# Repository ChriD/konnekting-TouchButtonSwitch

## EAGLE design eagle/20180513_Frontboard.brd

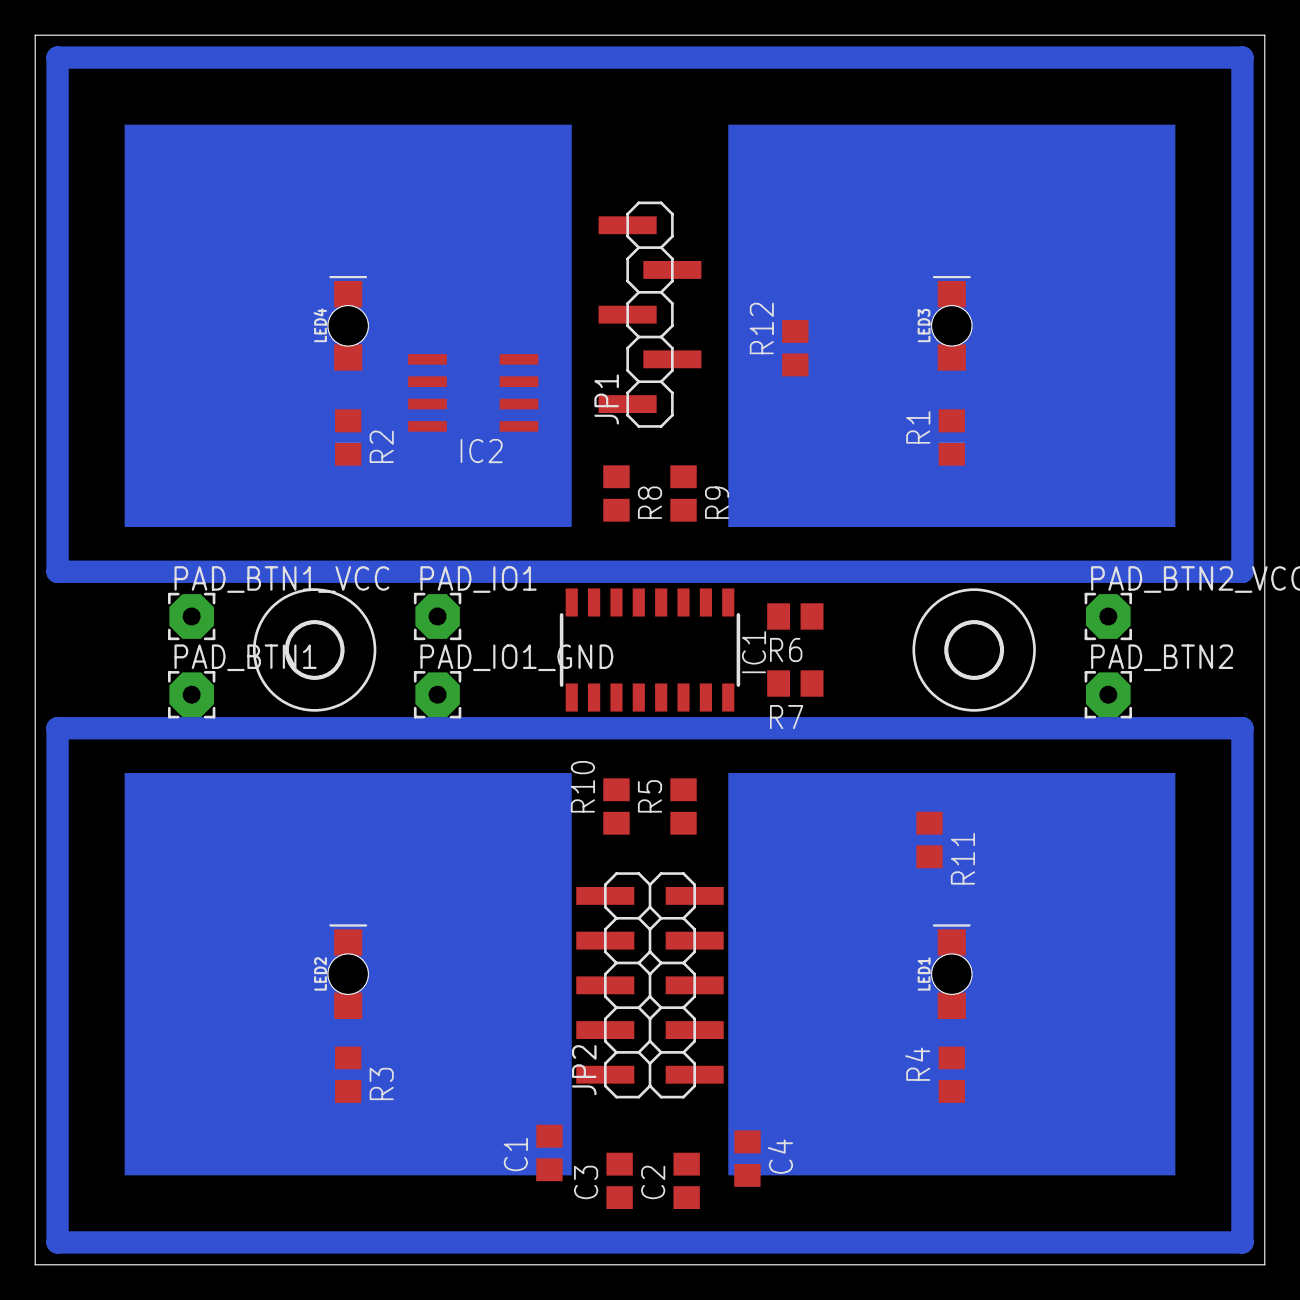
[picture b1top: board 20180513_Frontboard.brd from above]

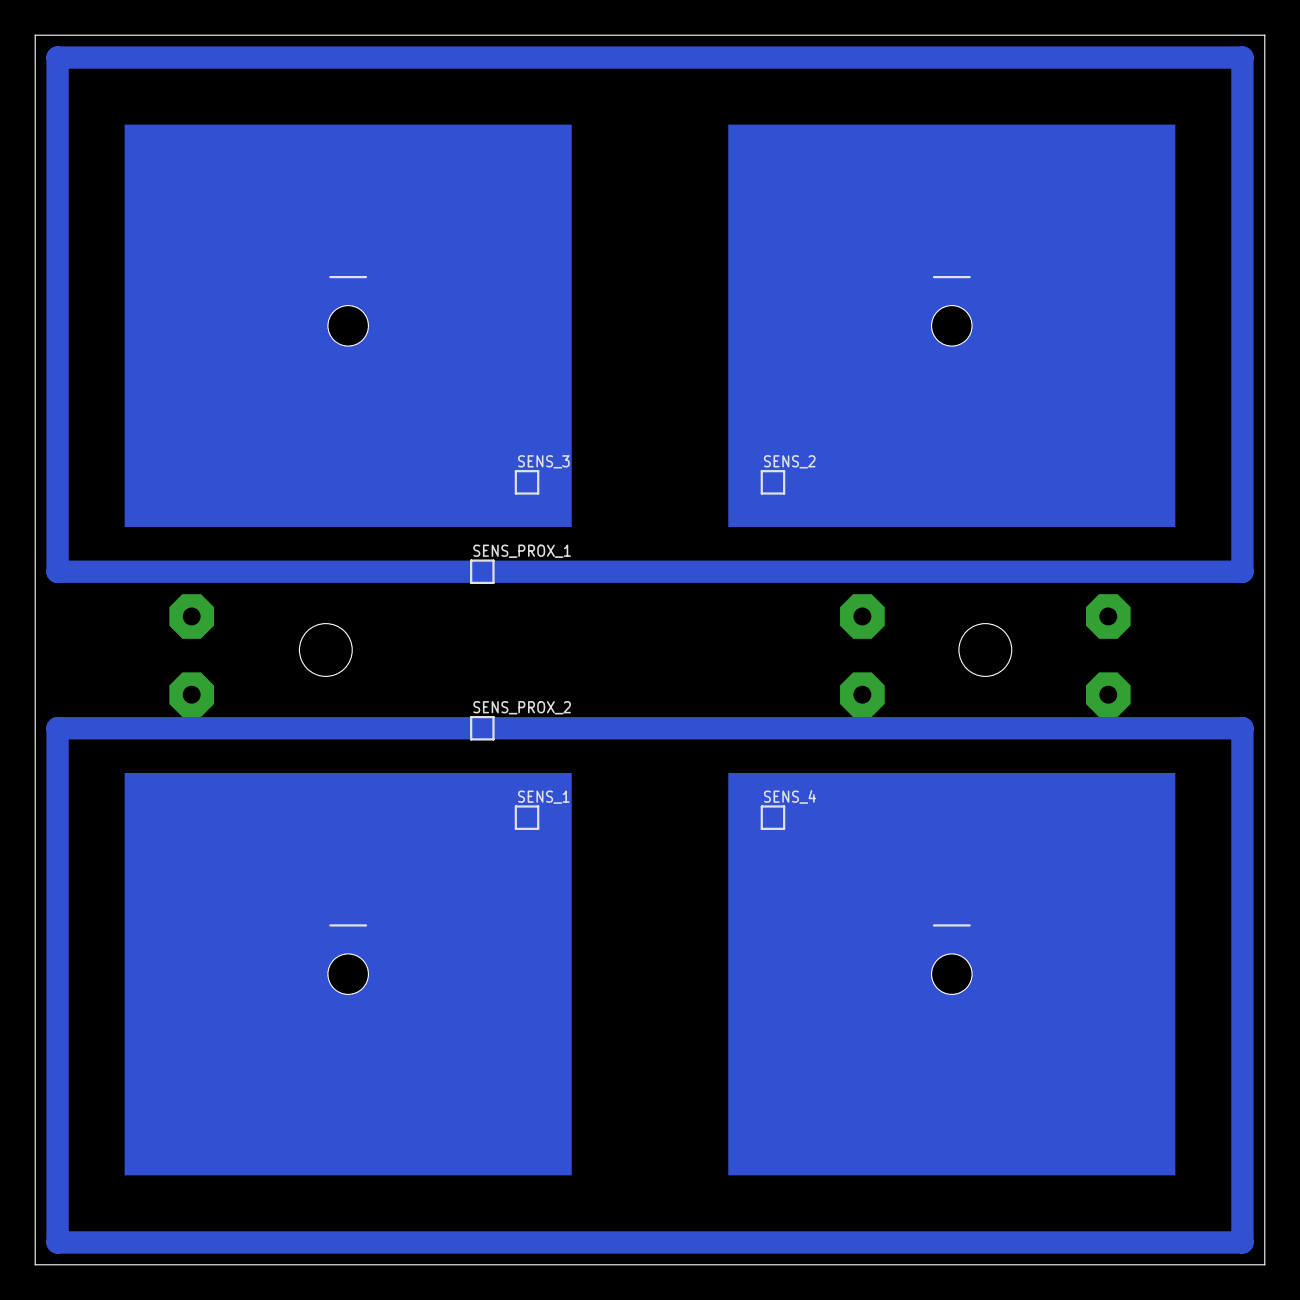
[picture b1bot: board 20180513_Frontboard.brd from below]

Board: 2 copper layers, 69.8 x 69.8 mm, 38 parts (6 on the bottom side), 33 nets.

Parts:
C1, C3: 0.1uf; C0805
C2: 1uf; C0805
C4: 2.2nf; C0805
IC1: CY8CMBR3110-SX2I; SOIC127P600X173-16N
IC2: LM35DM; SO08
JP1: I2C; 1X05SMD
JP2: IOS; 2X05SMD
LED1, LED2, LED3, LED4: WHITE; LED-1206-BOTTOM
PAD_BTN1, PAD_BTN1_VCC: BTN1; 2,54/1,0
PAD_BTN2, PAD_BTN2_VCC: BTN2; 2,54/1,0
PAD_IO1, PAD_IO1_GND: IO1; 2,54/1,0
R1, R2, R3, R4, R11, R12: 330E; R0805
R5, R6, R7, R8, R9, R10: 560E; R0805
SENS_1: SENS_1; WPAD-1-0603
SENS_2: SENS_2; WPAD-1-0603
SENS_3: SENS_3; WPAD-1-0603
SENS_4: SENS_4; WPAD-1-0603
SENS_PROX_1, SENS_PROX_2: SENS_PROX; WPAD-1-0603
U$1, U$2: 3,0

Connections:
BTN1: JP2.9, PAD_BTN1.1
BTN2: JP2.10, PAD_BTN2.1
GND: C1.2, C2.2, C3.2, C4.2, IC1.8, IC1.13, IC1.15, IC2.4, JP1.2, LED1.C, LED2.C, LED3.C, LED4.C, PAD_IO1_GND.1
HOST_INT: IC1.14, JP1.3
I2C_SCL: JP1.4, R11.2
I2C_SDA: JP1.5, R12.2
IO1: JP2.7, PAD_IO1.1
LED1: JP2.1, R4.1
LED2: JP2.2, R3.1
LED3: JP2.3, R1.1
LED4: JP2.4, R2.1
unnamed: IC1.9, R8.2
unnamed: IC1.10, R9.2
unnamed: IC1.11, R10.2
unnamed: IC1.1, R12.1
unnamed: IC1.2, R11.1
unnamed: IC1.3, R6.2
unnamed: IC1.12, R5.2
unnamed: C3.1, IC1.6
unnamed: C4.1, IC1.5
unnamed: IC1.4, R7.2
unnamed: LED4.A, R2.2
unnamed: LED1.A, R4.2
unnamed: LED2.A, R3.2
unnamed: LED3.A, R1.2
SENS_1: R5.1, SENS_1.1
SENS_2: R8.1, SENS_2.1
SENS_3: R9.1, SENS_3.1
SENS_4: R10.1, SENS_4.1
SENS_PROX_1: R6.1, SENS_PROX_1.1
SENS_PROX_2: R7.1, SENS_PROX_2.1
TMP: IC2.1, JP2.8
VCC: C1.1, C2.1, IC1.7, IC2.8, JP1.1, PAD_BTN1_VCC.1, PAD_BTN2_VCC.1

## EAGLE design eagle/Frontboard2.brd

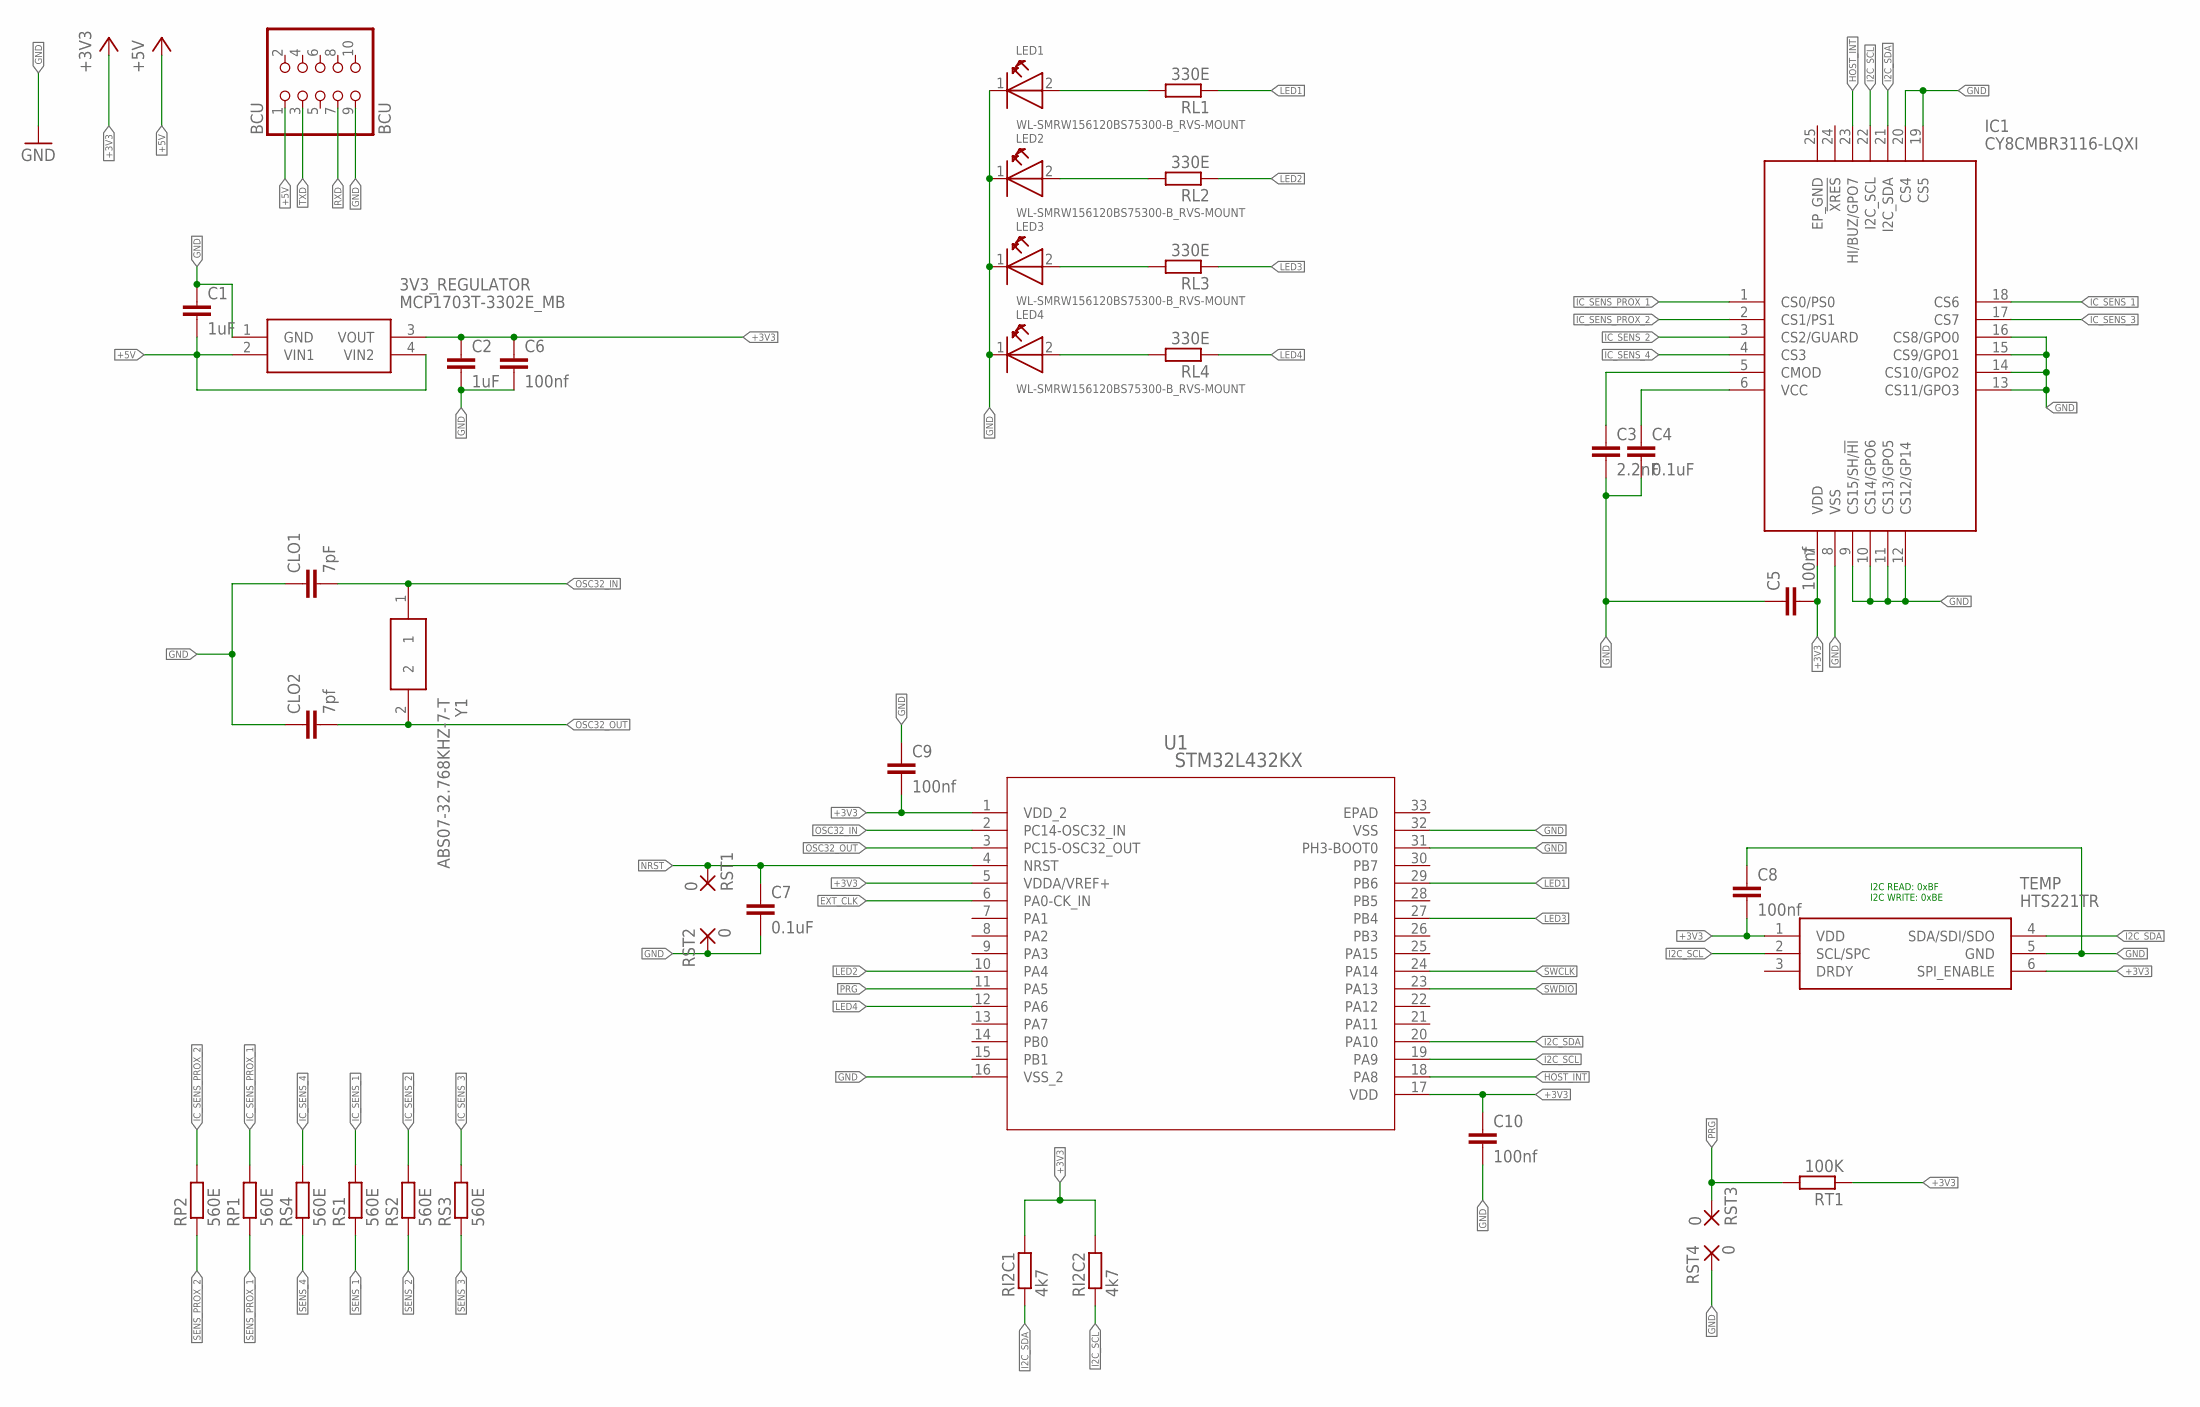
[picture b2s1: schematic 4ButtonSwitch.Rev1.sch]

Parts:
3V3_REGULATOR: MCP1703T-3302E_MB; SOT-89(MB)
BCU: BCU; 2X05SMD
C1, C2: 1uF; C0402
C3: 2.2nF; C0402
C4, C7: 0.1uF; C0402
C5, C6, C8, C9, C10: 100nf; C0402
CLO1: 7pF; C0402
CLO2: 7pf; C0402
IC1: CY8CMBR3116-LQXI; QFN50P400X400X60-25N
LED1, LED2, LED3, LED4: WL-SMRW156120BS75300-B_RVS-MOUNT; WL-SMRW-1206-CYLDR-REVERSE-MOUNT
RI2C1, RI2C2: 4k7; R0402
RL1, RL2, RL3, RL4: 330E; R0402
RP1, RP2: 560E; R0402
RS1, RS2, RS3, RS4: 560E; R0402
RST1, RST2, RST3, RST4: 0; SMD2,54-5,08
RT1: 100K; R0402
TEMP: HTS221TR; HLGA-6L
U1: STM32L432KX; UFQFPN32-5X5MM
Y1: ABS07-32.768KHZ-7-T; ABS-07

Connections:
+3V3: 3V3_REGULATOR.3 (VOUT), C2.1, C5.2, C6.1, C8.2, C9.2, C10.1, IC1.7 (VDD), RI2C1.2, RI2C2.2, RT1.1, TEMP.1 (VDD), TEMP.6 (SPI_ENABLE), U1.1 (VDD_2), U1.5 (VDDA/VREF+), U1.17 (VDD)
+5V: 3V3_REGULATOR.2 (VIN1), 3V3_REGULATOR.4 (VIN2), BCU.1, C1.2
CMOD: C3.1, IC1.5 (CMOD)
EP_GND: IC1.25 (EP_GND)
EXT_CLK: U1.6 (PA0-CK_IN)
GND: 3V3_REGULATOR.1 (GND), BCU.9, C1.1, C2.2, C3.2, C4.2, C5.1, C6.2, C7.2, C8.1, C9.1, C10.2, CLO1.1, CLO2.1, IC1.8 (VSS), IC1.9 (CS15/SH/!HI), IC1.10 (CS14/GPO6), IC1.11 (CS13/GPO5), IC1.12 (CS12/GP14), IC1.13 (CS11/GPO3), IC1.14 (CS10/GPO2), IC1.15 (CS9/GPO1), IC1.16 (CS8/GPO0), IC1.19 (CS5), IC1.20 (CS4), LED1.1 (K), LED2.1 (K), LED3.1 (K), LED4.1 (K), RST2.1, RST4.1, TEMP.5 (GND), U1.16 (VSS_2), U1.31 (PH3-BOOT0), U1.32 (VSS)
HOST_INT: IC1.23 (HI/BUZ/GPO7), U1.18 (PA8)
I2C_SCL: IC1.22 (I2C_SCL), RI2C2.1, TEMP.2 (SCL/SPC), U1.19 (PA9)
I2C_SDA: IC1.21 (I2C_SDA), RI2C1.1, TEMP.4 (SDA/SDI/SDO), U1.20 (PA10)
IC_SENS_1: IC1.18 (CS6), RS1.2
IC_SENS_2: IC1.3 (CS2/GUARD), RS2.2
IC_SENS_3: IC1.17 (CS7), RS3.2
IC_SENS_4: IC1.4 (CS3), RS4.2
IC_SENS_PROX_1: IC1.1 (CS0/PS0), RP1.2
IC_SENS_PROX_2: IC1.2 (CS1/PS1), RP2.2
LED1: RL1.1, U1.29 (PB6)
LED2: RL2.1, U1.10 (PA4)
LED3: RL3.1, U1.27 (PB4)
LED4: RL4.1, U1.12 (PA6)
unnamed: LED1.2 (A), RL1.2
unnamed: LED2.2 (A), RL2.2
unnamed: LED3.2 (A), RL3.2
unnamed: LED4.2 (A), RL4.2
NRST: C7.1, RST1.1, U1.4 (NRST)
OSC32_IN: CLO1.2, U1.2 (PC14-OSC32_IN), Y1.1
OSC32_OUT: CLO2.2, U1.3 (PC15-OSC32_OUT), Y1.2
PRG: RST3.1, RT1.2, U1.11 (PA5)
RXD: BCU.7
SENS_1: RS1.1
SENS_2: RS2.1
SENS_3: RS3.1
SENS_4: RS4.1
SENS_PROX_1: RP1.1
SENS_PROX_2: RP2.1
SWCLK: U1.24 (PA14)
SWDIO: U1.23 (PA13)
TXD: BCU.3
VCC: C4.1, IC1.6 (VCC)

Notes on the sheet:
I2C READ: 0xBF I2C WRITE: 0xBE

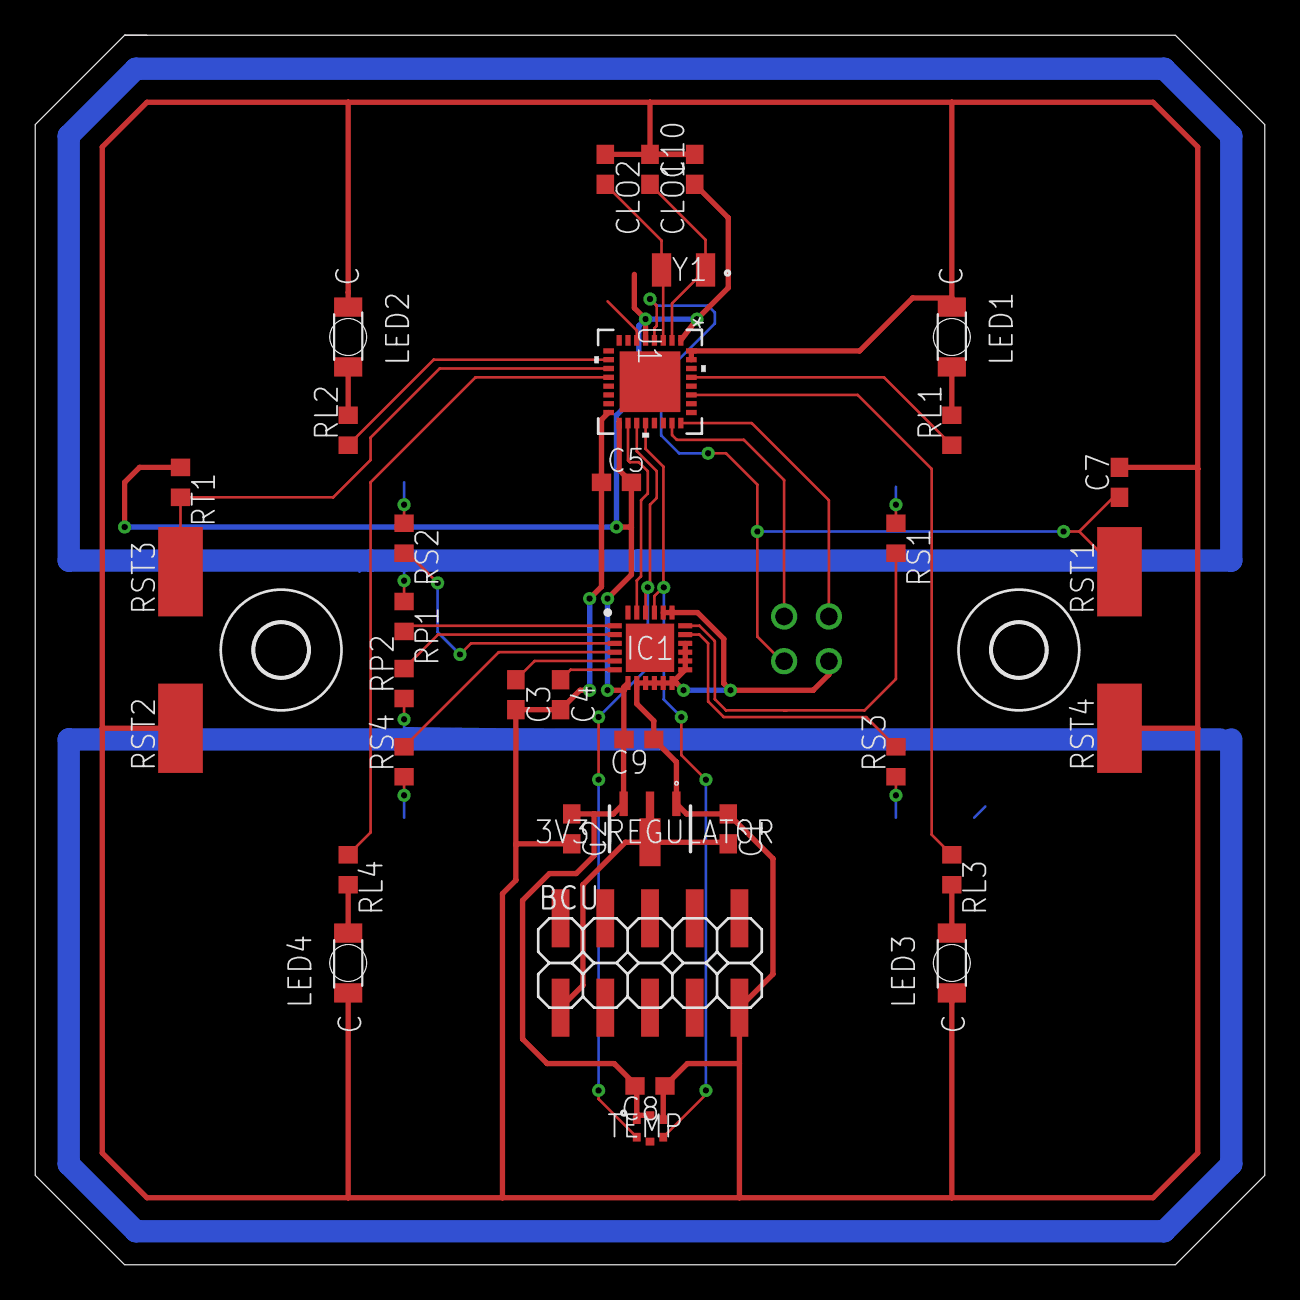
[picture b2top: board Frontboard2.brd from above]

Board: 2 copper layers, 69.8 x 69.8 mm, 38 parts (0 on the bottom side), 26 nets.

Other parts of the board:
U$1, U$2: 3,0

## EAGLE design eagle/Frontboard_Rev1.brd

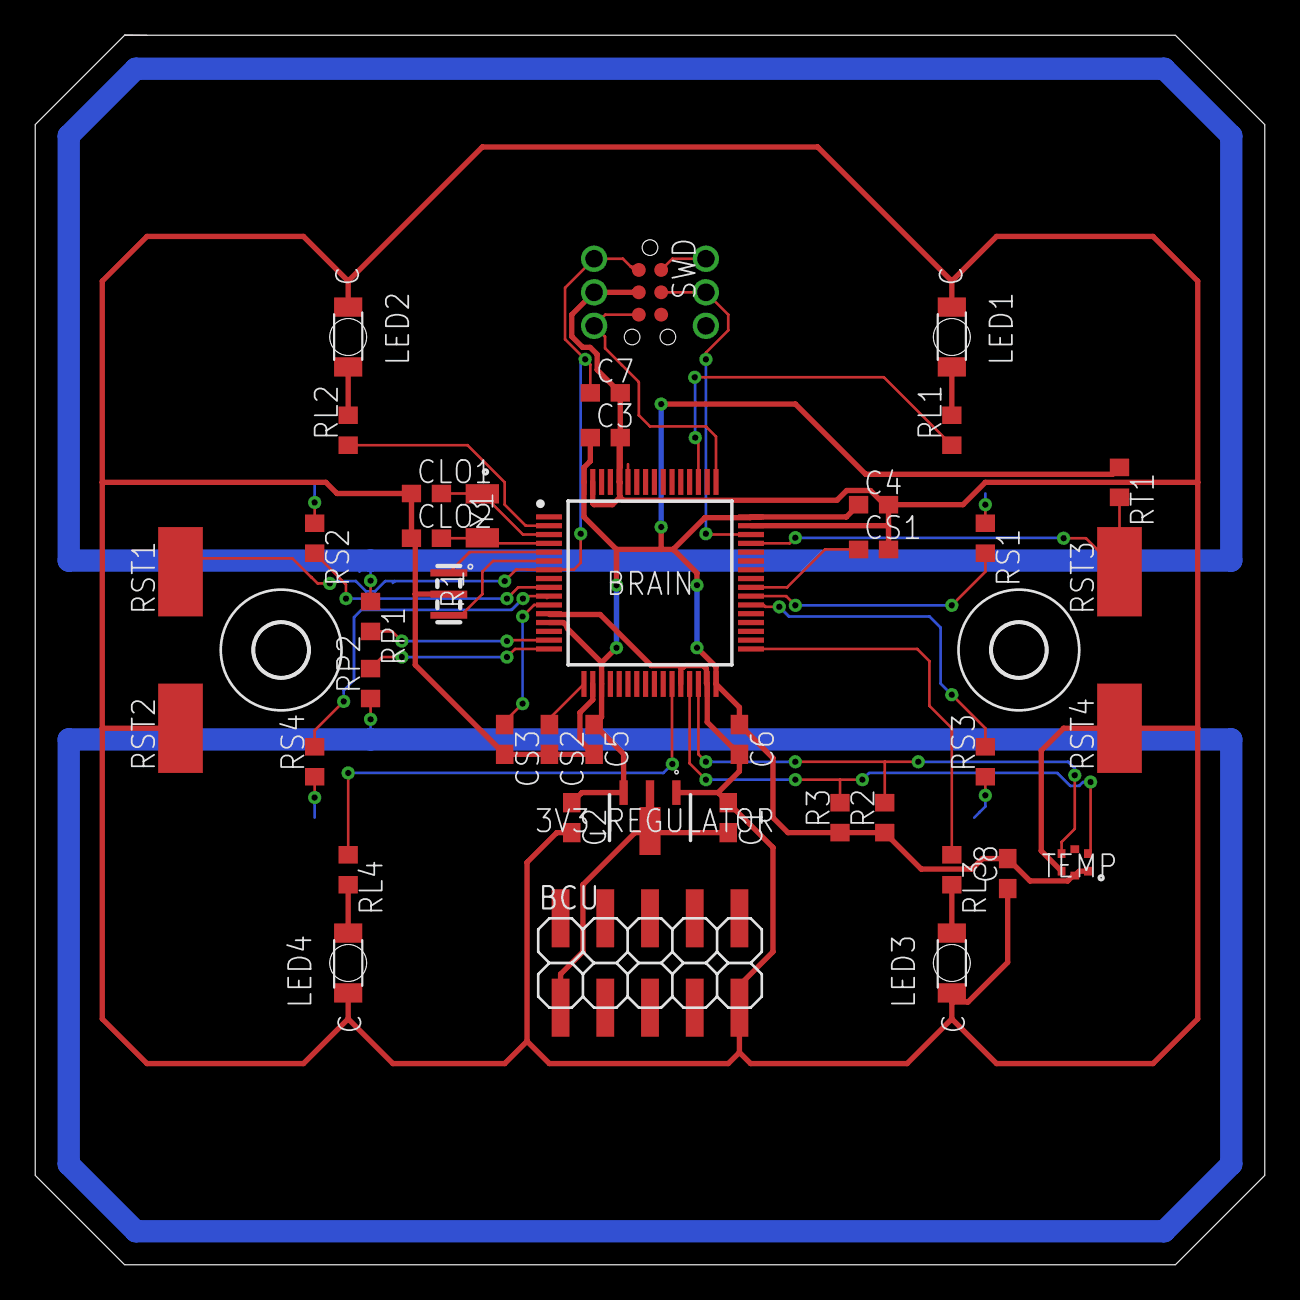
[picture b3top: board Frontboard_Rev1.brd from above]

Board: 2 copper layers, 69.8 x 69.8 mm, 43 parts (0 on the bottom side), 30 nets.

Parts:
3V3_REGULATOR: MCP1703T-3302E_MB; SOT-89(MB)
BCU: BCU; 2X05SMD
BRAIN: STM32L152RET6; QFP50P1200X1200X160-64N
C1, C2: 1uF; C0603
C3, C4, C5, C6, C8: 100nf; C0603
C7: 0.1uF; C0603
CLO1: 7pF; C0603
CLO2: 7pf; C0603
CS1, CS2, CS3: 47nF; C0603
LED1, LED2, LED3, LED4: WL-SMRW156120BS75300-B_RVS-MOUNT; WL-SMRW-1206-CYLDR-REVERSE-MOUNT
R1: CSTCE8M00G55-R0; CSTCE12M0G55-R0
R2, R3: 4.7k; R0603
RL1, RL2, RL3, RL4: 330E; R0603
RP1, RP2: 330E; R0603
RS1, RS2, RS3, RS4: 330E; R0603
RST1, RST2, RST3, RST4: 0; SMD2,54-5,08
RT1: 100K; R0603
SWD: SWD; TC2030-MCP-NL
TEMP: HTS221TR; HLGA-6L
U$1, U$2: 3,0
Y1: ABS07-32.768KHZ-7-T; ABS-07

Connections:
+3V3: 3V3_REGULATOR.3, BRAIN.13, BRAIN.19, BRAIN.32, BRAIN.48, BRAIN.64, C2.1, C3.1, C4.1, C5.1, C6.1, C8.2, R2.1, R3.1, RT1.1, TEMP.1, TEMP.6
+5V: 3V3_REGULATOR.2, 3V3_REGULATOR.4, BCU.1, C1.2
G1_IO2: BRAIN.15, RP1.2
G1_IO3: BRAIN.16, RP2.2
G1_IO4: BRAIN.17, CS2.1
G8_IO2: BRAIN.9, RS2.2
G8_IO3: BRAIN.10, RS4.2
G8_IO4: BRAIN.11, CS3.1
G10_IO2: BRAIN.38, RS3.2
G10_IO3: BRAIN.39, RS1.2
G10_IO4: BRAIN.40, CS1.1
GND: 3V3_REGULATOR.1, BCU.9, BRAIN.12, BRAIN.18, BRAIN.28, BRAIN.31, BRAIN.47, BRAIN.60, BRAIN.63, C1.1, C2.2, C3.2, C4.2, C5.2, C6.2, C7.2, C8.1, CLO1.1, CLO2.1, CS1.2, CS2.2, CS3.2, LED1.1, LED2.1, LED3.1, LED4.1, R1.2, RST2.1, RST4.1, SWD.3, TEMP.5
I2C2_SCL: BRAIN.29, R3.2, TEMP.2
I2C2_SDA: BRAIN.30, R2.2, TEMP.4
LED1: BRAIN.51, RL1.1
LED2: BRAIN.2, RL2.1
LED3: BRAIN.33, RL3.1
LED4: BRAIN.27, RL4.1
unnamed: LED1.2, RL1.2
unnamed: LED2.2, RL2.2
unnamed: LED3.2, RL3.2
unnamed: LED4.2, RL4.2
NRST: BRAIN.7, C7.1, RST1.1, SWD.1
OSC32_IN: BRAIN.3, CLO1.2, Y1.1
OSC32_OUT: BRAIN.4, CLO2.2, Y1.2
OSC_IN: BRAIN.5, R1.1
OSC_OUT: BRAIN.6, R1.3
PRG: BRAIN.45, RST3.1, RT1.2
SWCLK: BRAIN.49, SWD.5
SWDIO: BRAIN.46, SWD.4

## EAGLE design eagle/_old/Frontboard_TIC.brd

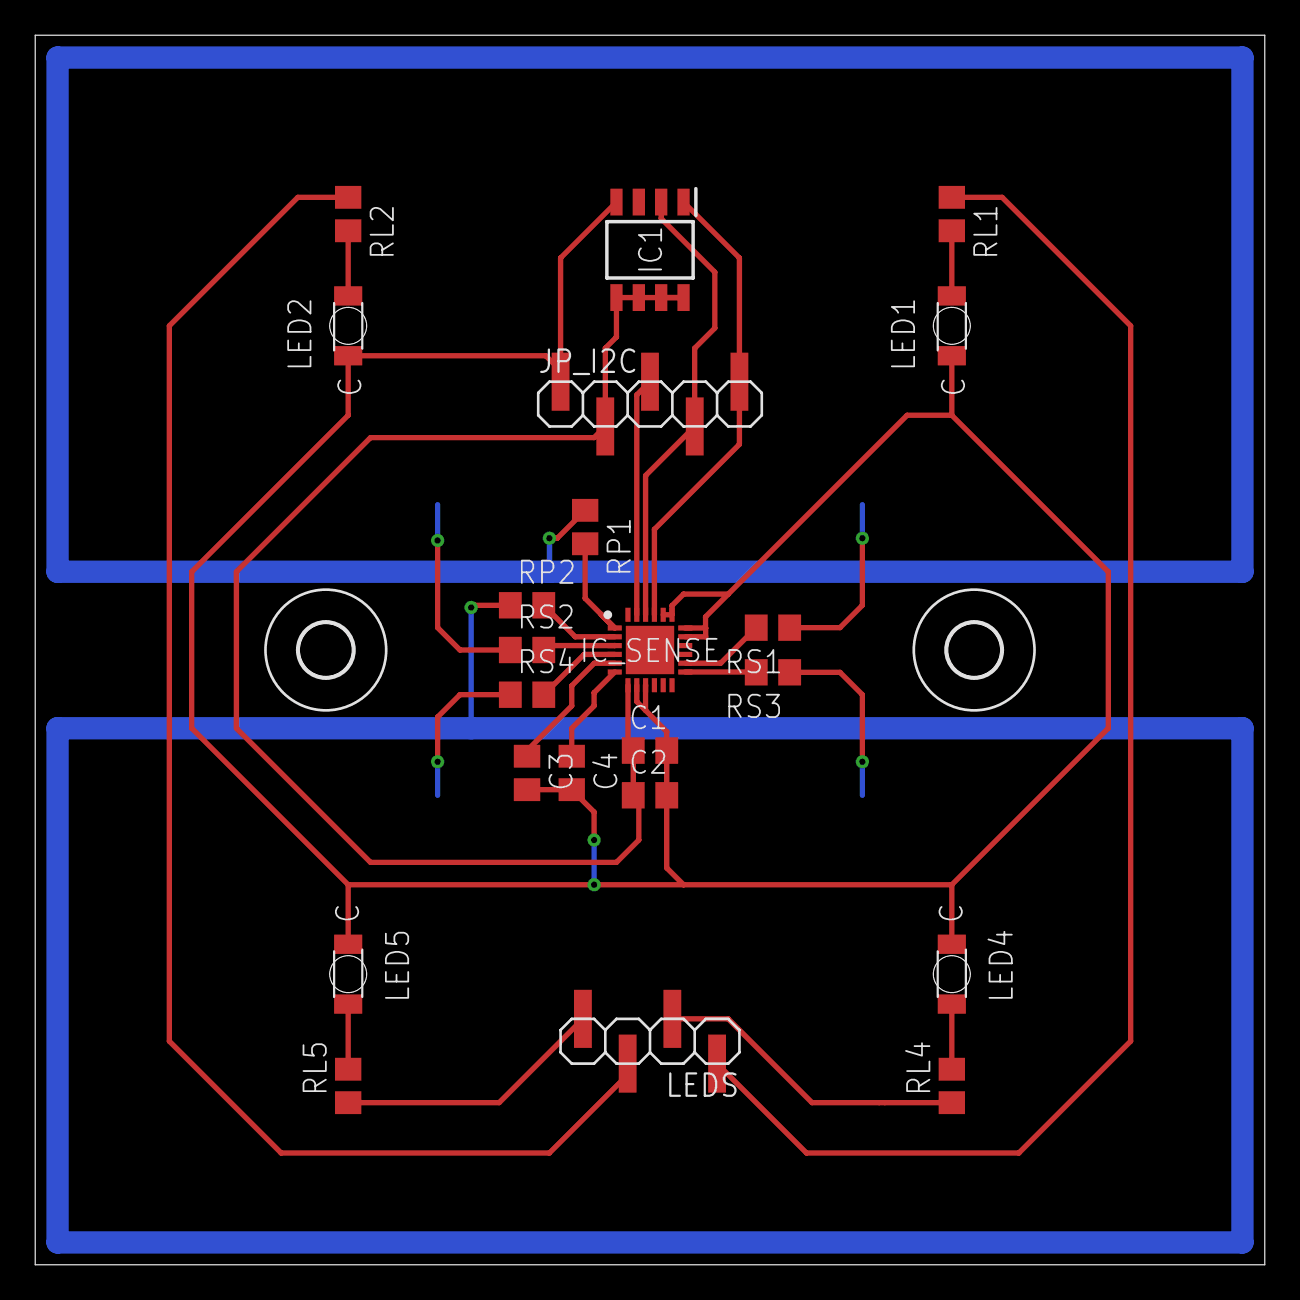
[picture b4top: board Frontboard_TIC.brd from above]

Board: 2 copper layers, 69.8 x 69.8 mm, 24 parts (0 on the bottom side), 21 nets.

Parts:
C1, C4: 0.1uf; C0805
C2: 1uf; C0805
C3: 2.2nf; C0805
IC1: NCT75DR2G; SOIC127P600X175-8N
IC_SENSE: CY8CMBR3116-LQXIT; QFN50P400X400X60-25N
JP_I2C: I2C; 1X05SMD
LED1, LED2, LED4, LED5: WL-SMRW156120BS75300-B_RVS-MOUNT; WL-SMRW-1206-CYLDR-REVERSE-MOUNT
LEDS: LEDS; 1X04SMD
RL1, RL2, RL4, RL5: 330E; R0805
RP1, RP2: 560E; R0805
RS1, RS2, RS3, RS4: 560E; R0805
U$1, U$2: 3,0

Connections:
GND: C1.2, C2.2, C3.2, C4.2, IC1.4, IC_SENSE.8, IC_SENSE.9, IC_SENSE.17, IC_SENSE.18, IC_SENSE.19, IC_SENSE.20, JP_I2C.1, LED1.1, LED2.1, LED4.1, LED5.1
HOST_INT: IC_SENSE.23, JP_I2C.3
I2C_SCL: IC1.2, IC_SENSE.22, JP_I2C.4
I2C_SDA: IC1.1, IC_SENSE.21, JP_I2C.5
LED1: LEDS.1, RL1.1
LED2: LEDS.3, RL2.1
LED4: LEDS.2, RL4.1
LED5: LEDS.4, RL5.1
unnamed: LED1.2, RL1.2
unnamed: LED2.2, RL2.2
unnamed: IC_SENSE.14, RS1.2
unnamed: IC_SENSE.13, RS3.2
unnamed: IC_SENSE.1, RP1.2
unnamed: IC_SENSE.2, RP2.2
unnamed: IC_SENSE.4, RS4.2
unnamed: IC_SENSE.3, RS2.2
unnamed: LED4.2, RL4.2
unnamed: LED5.2, RL5.2
unnamed: C4.1, IC_SENSE.6
unnamed: C3.1, IC_SENSE.5
VCC: C1.1, C2.1, IC1.5, IC1.6, IC1.7, IC1.8, IC_SENSE.7, JP_I2C.2

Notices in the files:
parts and their libraries:
PatternAgents-ProtoPads: License : http://creativecommons.org/licenses/by-sa/4.0
(Creative Commons 4.0)
SparkFun-LED: Licensing: Creative Commons ShareAlike 4.0 International - https://creativecommons.org/licenses/by-sa/4.0
Wurth_Elektronik_Optoelectronics_rev15b: Copyright: Würth Elektronik
